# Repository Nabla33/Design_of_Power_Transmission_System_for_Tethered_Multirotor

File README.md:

# Design_of_Power_Transmission_System_for_Tethered_Multirotor
The design of PCB and schematic for the power transmission system for the tethered drone

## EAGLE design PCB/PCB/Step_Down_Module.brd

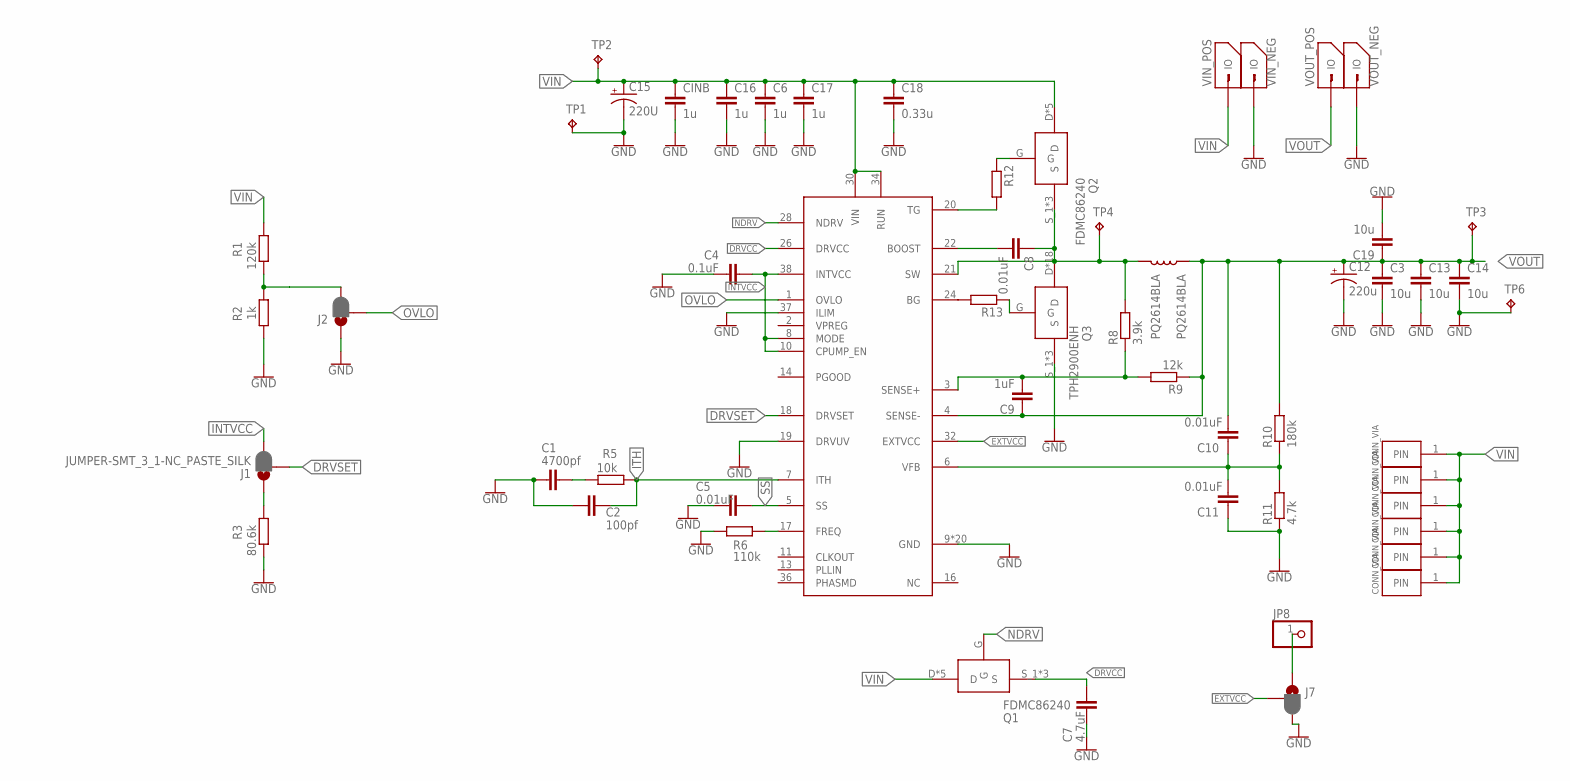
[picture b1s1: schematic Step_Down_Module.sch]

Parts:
C1: 4700pf; C0805
C2: 100pf; C0805
C3, C13, C14, C19: 10u; 1210
C4: 0.1uF; C0805
C5, C8, C10, C11: 0.01uF; C0805
C6, C16, C17: 1u; C2220K
C7: 4.7uF; C0805
C9: 1uF; C0805
C12: 220u; CPOL-RADIAL-5MM-10MM
C15: 220U; CPOL-RADIAL-7.5MM-18MM
C18: 0.33u; C1812
CINB: 1u; C2220K
J1, J2, J7: JUMPER-SMT_3_1-NC_PASTE_SILK; SMT-JUMPER_3_1-NC_PASTE_SILK
JP8: PINHD-1X1; 1X01
L1: PQ2614BLA
Q1, Q2: FDMC86240; 8-MLP/POWERWFDN
Q3: TPH2900ENH; SOP_ADVANCE
R1: 120k; R0805
R2: 1k; R0805
R3: 80.6k; R0805
R5: 10k; R0805
R6: 110k; R0805
R8: 3.9k; 0204/5
R9: 12k; 0204/5
R10: 180k; R0805
R11: 4.7k; R0805
R12, R13: R-EU_R0805; R0805
TP1, TP2, TP3, TP4, TP6: TPTP16R; TP16R
U1: LTC3895_STEP_DOWN_DC-DC_CONVERTERSMD_TSSOP; 38_LEAD_TSSOP(FE38)
U$1, U$2, U$3, U$4, U$5, U$6: CONN_VIA
VIN_NEG: IO_PAD_SINGLE; IO_SINGLE
VIN_POS: IO_PAD_SINGLE; IO_SINGLE
VOUT_NEG: IO_PAD_SINGLE; IO_SINGLE
VOUT_POS: IO_PAD_SINGLE; IO_SINGLE

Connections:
BOOST: C8.2, U1.22 (BOOST)
DRVCC: C7.1, Q1.S_1 (S), Q1.S_2 (S), Q1.S_3 (S), U1.26 (DRVCC)
DRVSET: J1.2, U1.18 (DRVSET)
EXTVCC: J7.2, U1.32 (EXTVCC)
FREQ: R6.2, U1.17 (FREQ)
G2: R12.2, U1.20 (TG)
G3: R13.2, U1.24 (BG)
GND: C1.2, C2.2, C3.2, C4.1, C5.2, C6.2, C7.2, C11.1, C12.-, C13.2, C14.2, C15.-, C16.2, C17.2, C18.2, C19.2, CINB.2, J2.1, J7.3, Q3.S_1 (S), Q3.S_2 (S), Q3.S_3 (S), R2.2, R3.2, R6.1, R11.1, TP1.TP, TP6.TP, U1.9 (GND), U1.12 (GND), U1.15 (GND), U1.19 (DRVUV), U1.37 (ILIM), U1.39 (GND), U1.39_B (GND), U1.PWR_PAD1 (GND), U1.PWR_PAD2 (GND), U1.PWR_PAD3 (GND), U1.PWR_PAD4 (GND), U1.PWR_PAD5 (GND), U1.PWR_PAD6 (GND), U1.PWR_PAD7 (GND), U1.PWR_PAD8 (GND), U1.PWR_PAD9 (GND), U1.PWR_PAD10 (GND), U1.PWR_PAD11 (GND), U1.PWR_PAD12 (GND), U1.PWR_PAD13 (GND), U1.PWR_PAD14 (GND), U1.PWR_PAD15 (GND), VIN_NEG.1, VIN_NEG.2, VIN_NEG.3, VIN_NEG.4, VIN_NEG.5, VIN_NEG.6, VIN_NEG.7, VIN_NEG.8, VIN_NEG.9, VIN_NEG.10, VIN_NEG.11, VIN_NEG.12, VIN_NEG.13, VIN_NEG.14, VIN_NEG.15, VIN_NEG.16, VIN_NEG.17, VIN_NEG.18, VIN_NEG.19, VIN_NEG.20, VIN_NEG.IO1, VIN_NEG.IO2, VOUT_NEG.1, VOUT_NEG.2, VOUT_NEG.3, VOUT_NEG.4, VOUT_NEG.5, VOUT_NEG.6, VOUT_NEG.7, VOUT_NEG.8, VOUT_NEG.9, VOUT_NEG.10, VOUT_NEG.11, VOUT_NEG.12, VOUT_NEG.13, VOUT_NEG.14, VOUT_NEG.15, VOUT_NEG.16, VOUT_NEG.17, VOUT_NEG.18, VOUT_NEG.19, VOUT_NEG.20, VOUT_NEG.IO1, VOUT_NEG.IO2
INTVCC: C4.2, J1.3, U1.8 (MODE), U1.10 (CPUMP_EN), U1.38 (INTVCC)
ITH: C2.1, R5.1, U1.7 (ITH)
unnamed: Q2.G, R12.1
unnamed: Q3.G, R13.1
unnamed: J1.1, R3.1
unnamed: J2.3, R1.2, R2.1
unnamed: C1.1, R5.2
unnamed: J7.1, JP8.1
NDRV: Q1.G, U1.28 (NDRV)
OVLO: J2.2, U1.1 (OVLO)
S+: C9.2, R8.1, R9.2, U1.3 (SENSE+)
SS: C5.1, U1.5 (SS)
SW: C8.1, L1.P1, Q2.S_1 (S), Q2.S_2 (S), Q2.S_3 (S), Q3.D, Q3.D1 (D), Q3.D_1 (D), Q3.D_2 (D), Q3.D_3 (D), Q3.D_4 (D), Q3.PWR_PAD1 (D), Q3.PWR_PAD2 (D), Q3.PWR_PAD3 (D), Q3.PWR_PAD4 (D), Q3.PWR_PAD5 (D), Q3.PWR_PAD6 (D), Q3.PWR_PAD7 (D), Q3.PWR_PAD8 (D), Q3.PWR_PAD9 (D), Q3.PWR_PAD10 (D), Q3.PWR_PAD11 (D), Q3.PWR_PAD12 (D), R8.2, TP4.TP, U1.21 (SW)
VFB: C10.1, C11.2, R10.1, R11.2, U1.6 (VFB)
VIN: C6.1, C15.+, C16.1, C17.1, C18.1, CINB.1, Q1.D, Q1.D_1 (D), Q1.D_2 (D), Q1.D_3 (D), Q1.D_4 (D), Q2.D, Q2.D_1 (D), Q2.D_2 (D), Q2.D_3 (D), Q2.D_4 (D), R1.1, TP2.TP, U1.30 (VIN), U1.34 (RUN), U$1.1, U$2.1, U$3.1, U$4.1, U$5.1, U$6.1, VIN_POS.1, VIN_POS.2, VIN_POS.3, VIN_POS.4, VIN_POS.5, VIN_POS.6, VIN_POS.7, VIN_POS.8, VIN_POS.9, VIN_POS.10, VIN_POS.11, VIN_POS.12, VIN_POS.13, VIN_POS.14, VIN_POS.15, VIN_POS.16, VIN_POS.17, VIN_POS.18, VIN_POS.19, VIN_POS.20, VIN_POS.IO1, VIN_POS.IO2
VOUT: C3.1, C9.1, C10.2, C12.+, C13.1, C14.1, C19.1, L1.P2, R9.1, R10.2, TP3.TP, U1.4 (SENSE-), VOUT_POS.1, VOUT_POS.2, VOUT_POS.3, VOUT_POS.4, VOUT_POS.5, VOUT_POS.6, VOUT_POS.7, VOUT_POS.8, VOUT_POS.9, VOUT_POS.10, VOUT_POS.11, VOUT_POS.12, VOUT_POS.13, VOUT_POS.14, VOUT_POS.15, VOUT_POS.16, VOUT_POS.17, VOUT_POS.18, VOUT_POS.19, VOUT_POS.20, VOUT_POS.IO1, VOUT_POS.IO2

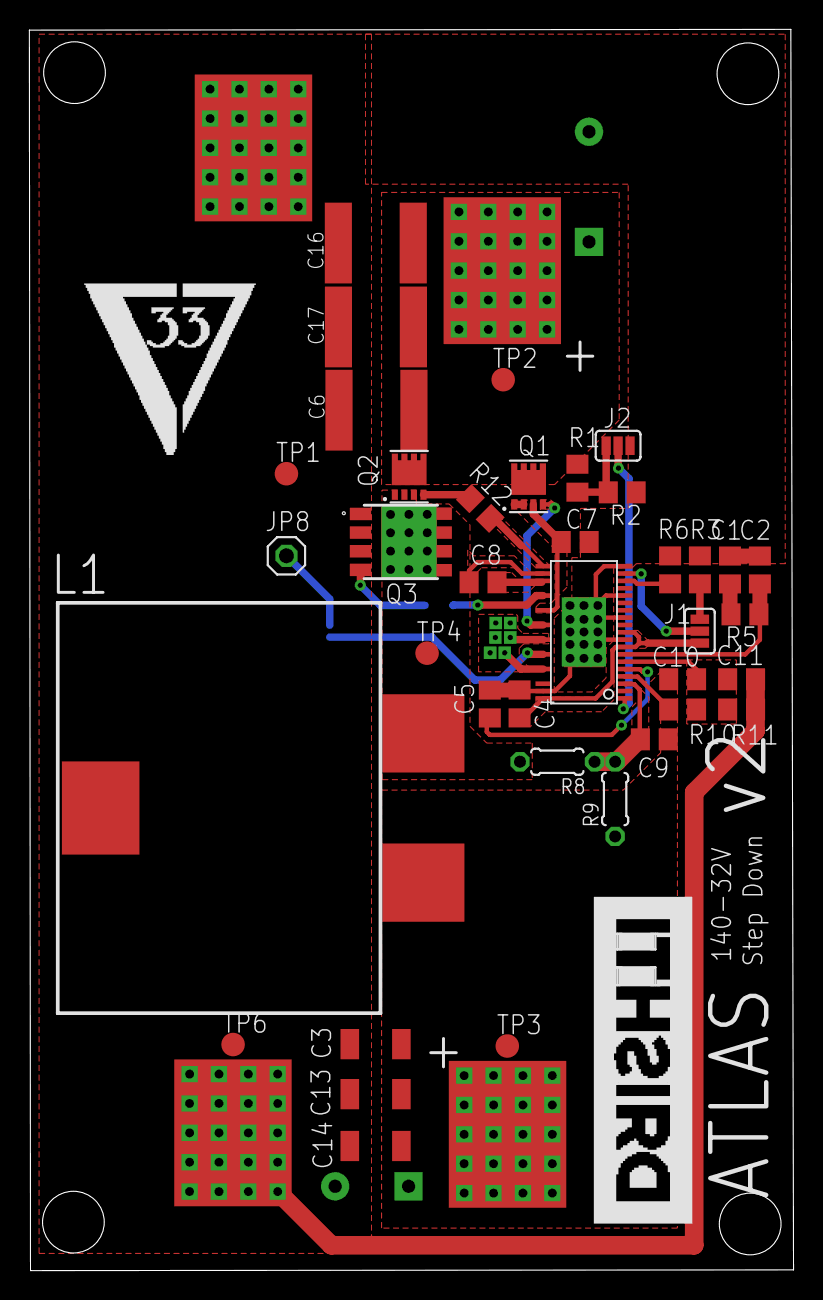
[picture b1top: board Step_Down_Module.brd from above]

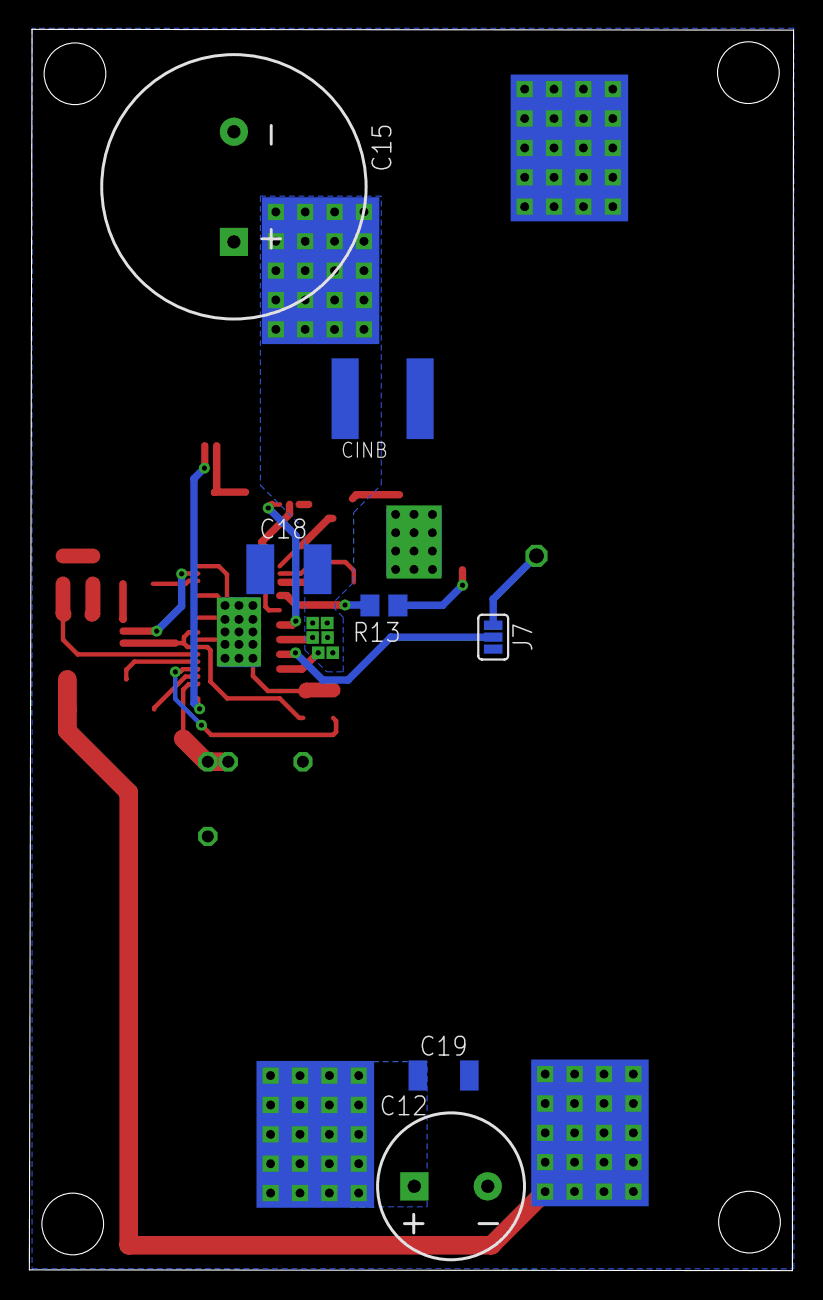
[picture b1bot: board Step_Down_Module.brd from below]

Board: 2 copper layers, 52.0 x 84.5 mm, 55 parts (7 on the bottom side), 24 nets.

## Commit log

2018-12-04 Added package for LTC3895, LTCAD design
2018-12-04 Created Eagle libraries for Switching MOSs and Inductor PQ2614BHA
2018-12-04 Updated switching MOS and inductor footprint
2018-12-04 Updated the mosfet designs
2018-12-05 Working on schematic, slightly updated mosfets
2018-12-06 Added thermal vias
2018-12-06 Corrected thermal pad error
2018-12-07 Working on schematic - functions of other pins
2018-12-07 Working on schematic - Added I/O capacitors
2018-12-09 Working on schematic - Added DRVCC transistor, made a lot of changes to the pin state
2018-12-12 Partial Layout of pins 1-20 (without Inductor and MOS)
2018-12-12 Removed folder: Adithya
2018-12-13 Initial routing of PCB with design considerations
2018-12-14 Finalized PCB - first iteration
2018-12-16 PCB Routing edits - moved bypass cap, changed trace widths
2018-12-17 PCB changes, added through hole part for RP, fixed pot error
2018-12-18 Fixed minor drc errors(Wire stub)
2018-12-18 PCB Component names renumbered and libraries updated with prefix
2019-01-13 WIP-PCB revision 2; without proper caps, polygons
2019-01-13 Commiting changes if any
2019-01-13 updatig input capacitor bank
2019-01-13 WIP-PCB revision 2; Major parts of layout done
2019-01-14 WIP:PCB revision 2; Move inductor and optimize SW Node area
2019-01-16 Corrected sense resistors, DRVCC trace
2019-01-17 Added electrolytics, test points
2019-01-25 PCB rev2 sent for manufacture

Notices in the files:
parts and their libraries:
SparkFun-Jumpers: Licensing: Creative Commons ShareAlike 4.0 International - https://creativecommons.org/licenses/by-sa/4.0
